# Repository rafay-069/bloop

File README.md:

# bloop
Bloop is a small desk pet that lives on a big colour screen connected to an ESP32. He has a cute face that blinks, looks around and reacts when you press his buttons, and he falls asleep when nobody talks to him. He is also useful: he shows the time, works as a study timer, tells the weather and air quality, reminds you to drink water, counts your study streak, shows messages sent from your phone, and even helps you make small decisions.
He also has a built-in Flappy Bird game.
# buttons 
POWER — Bloop on/off
PLAY — Pomodoro timer (short press) / mark study streak (long press)
WEATHER — Weather + air quality card
ORACLE — Decision helper
GAMES — Flappy Bird
#BOM
| Part | What it's for | Qty | Price | Link |
|---|---|---|---|---|
| ESP32 DevKit board 30-pin (CH9102X Type-C) | Brain board | 1 | $5.09 | [Robu](https://robu.in/product/30pin-ch9102x-esp-32-wifibluetooth-development-board-with-type-c-usb-interface/) |
| 3.5 inch TFT LCD touch module ILI9488 480x320 | Bloop's big colour screen | 1 | $12.15 | [Robu](https://robu.in/product/3-5-inch-spi-50pin-tft-lcd-touch-moduleili9488-driver-480x320-color-screen/) |
| Female header socket 1x8 2.54mm | Socket the screen plugs into | 1 | $0.20 | [Robu](https://robu.in/product/fh2-54-09-08pzd-xunpu-plugin1x8-pin-2-54mm-female-headers-rohs/) |
| Female header strip 1x40 2.54mm | Cut into two 1x15 ESP32 sockets | 1 | $0.20 | [Robu](https://robu.in/product/2-54mm-1x40-pin-female-single-row-header-strip-pack-of-10/) |
| Tactile push buttons 6x6x5 (pack of 10) | Bloop's five buttons | 1 | $0.22 | [Robu](https://robu.in/product/6x6x5-tactile-push-button-switch/) |
| Electrolytic capacitor 10uF 25V | Power smoothing by the screen socket | 1 | $0.20 | [Robu](https://robu.in/product/10-uf-25v-through-hole-electrolytic-capacitor-pack-of-40/) |
| Disc ceramic capacitor 100nF 50V | Power smoothing by the screen socket | 1 | $0.20 | [Robu](https://robu.in/product/100nf-50v-disc-capacitor/) |
| Red LED 3mm | Power light | 1 | $0.20 | [Robu](https://robu.in/product/204-10surc-s530-a3-l-everlight-elec-red-3mm-round-bulb-plugind3mm-led-indication-discrete-rohs/) |
| Chip resistor 1k 0805 | LED resistor | 1 | $0.20 | [Robu](https://robu.in/product/1k-ohm-1-4w-0805-surface-mount-chip-resistor-pack-of-10/) |
| **Total** | | | **$18.66** | *plus PCB fabrication, priced at order time* |

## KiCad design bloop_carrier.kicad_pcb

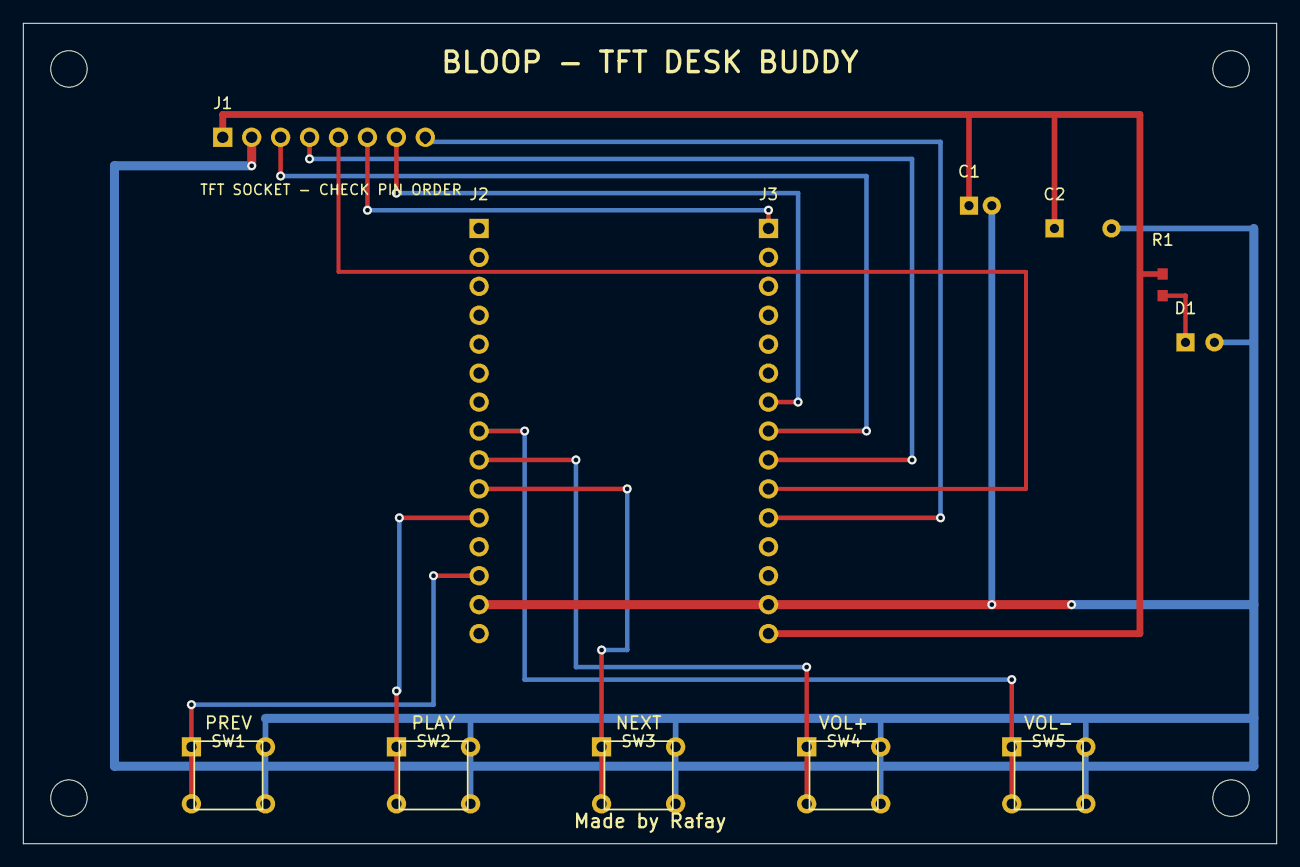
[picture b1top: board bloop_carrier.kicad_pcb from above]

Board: 3 copper layers, 110.0 x 72.0 mm, 12 parts (0 on the bottom side), 14 nets.

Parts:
C1: 10uF; C1
C2: 100nF; C2
D1: LED_RED; D1
J1: TFT_1x8_SOCKET; J1
J2: ESP32_LEFT; J2
J3: ESP32_RIGHT; J3
R1: 1k; R1
SW1: TACT_6x6; SW1
SW2: TACT_6x6; SW2
SW3: TACT_6x6; SW3
SW4: TACT_6x6; SW4
SW5: TACT_6x6; SW5

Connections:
+3V3: C1.1, C2.1, J1.1, J3.15, R1.1
BTN_DOWN: J2.8, SW5.1, SW5.2
BTN_LEFT: J2.13, SW1.1, SW1.2
BTN_PLAY: J2.11, SW2.1, SW2.2
BTN_RIGHT: J2.10, SW3.1, SW3.2
BTN_UP: J2.9, SW4.1, SW4.2
GND: C1.2, C2.2, D1.2, J1.2, J2.14, J3.14, SW1.3, SW1.4, SW2.3, SW2.4, SW3.3, SW3.4, SW4.3, SW4.4, SW5.3, SW5.4
LED_A: D1.1, R1.2
TFT_BL: J1.8, J3.11
TFT_CS: J1.3, J3.8
TFT_DC: J1.5, J3.10
TFT_MOSI: J1.6, J3.1
TFT_RST: J1.4, J3.9
TFT_SCK: J1.7, J3.7
